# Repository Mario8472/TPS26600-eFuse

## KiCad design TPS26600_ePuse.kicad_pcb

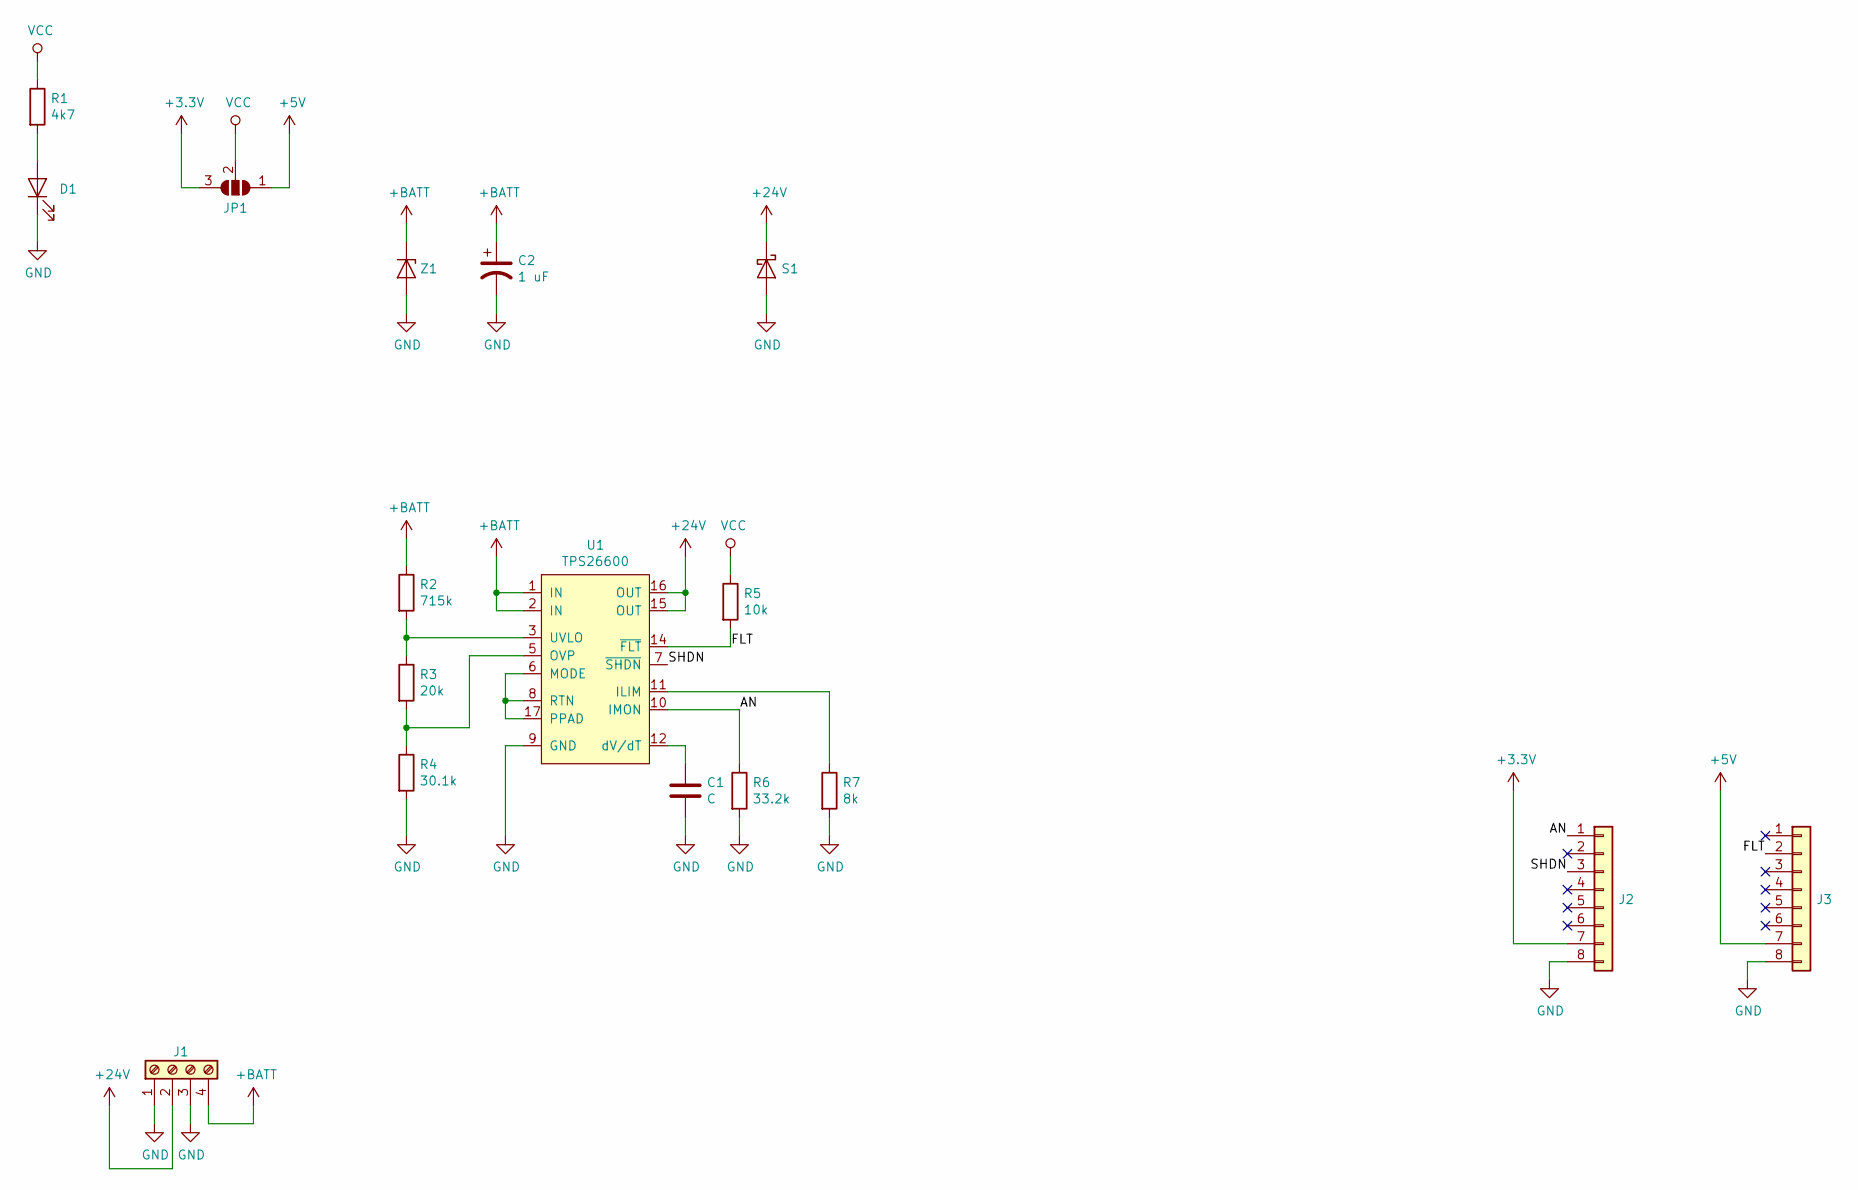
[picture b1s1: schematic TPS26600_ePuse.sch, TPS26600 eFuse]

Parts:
C1: C; C_0805_2012Metric
C2: 1 uF; C_1206_3216Metric
D1: LED; LED_0805_2012Metric
J1: Screw_Terminal_01x04; PCB_Screw_Terminal_5.08_4ways
J2, J3: Conn_01x08; PinHeader_1x08_P2.54mm_Vertical
JP1: SolderJumper_3_Open; Jumper_0805
R1: 4k7; R_0805_2012Metric
R2: 715k; R_0805_2012Metric
R3: 20k; R_0805_2012Metric
R4: 30.1k; R_0805_2012Metric
R5: 10k; R_0805_2012Metric
R6: 33.2k; R_0805_2012Metric
R7: 8k; R_0805_2012Metric
S1: D_Schottky; D_SMA
U1: TPS26600; HTSSOP-16-1EP_4.4x5mm_P0.65mm_EP3x3mm
Z1: D_Zener; D_SMA

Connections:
+3V3: J2.7, JP1.3 (B)
+5V: J3.7, JP1.1 (A)
+24V: J1.2, S1.1 (K), U1.15 (OUT), U1.16 (OUT)
+BATT: C2.1, J1.4, R2.1, U1.1 (IN), U1.2 (IN), Z1.1 (K)
/AN: J2.1, R6.1, U1.10 (IMON)
/FLT: J3.2, R5.2, U1.14 (~FLT)
/SHDN: J2.3, U1.7 (~SHDN)
GND: C1.2, C2.2, D1.1 (K), J1.1, J1.3, J2.8, J3.8, R4.2, R6.2, R7.2, S1.2 (A), U1.9 (GND), Z1.2 (A)
unnamed: C1.1, U1.12 (dV/dT)
unnamed: D1.2 (A), R1.2
unnamed: R2.2, R3.1, U1.3 (UVLO)
unnamed: R3.2, R4.1, U1.5 (OVP)
unnamed: R7.1, U1.11 (ILIM)
unnamed: U1.6 (MODE), U1.8 (RTN), U1.17 (PPAD)
VCC: JP1.2 (C), R1.1, R5.1

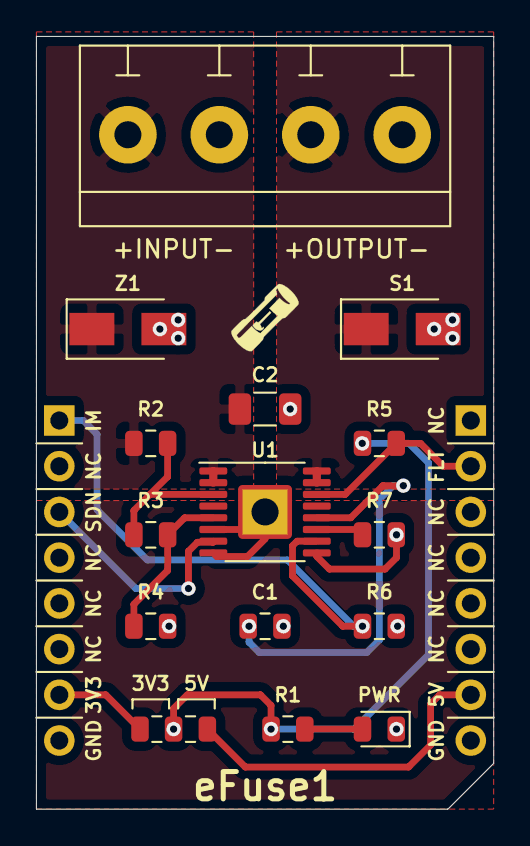
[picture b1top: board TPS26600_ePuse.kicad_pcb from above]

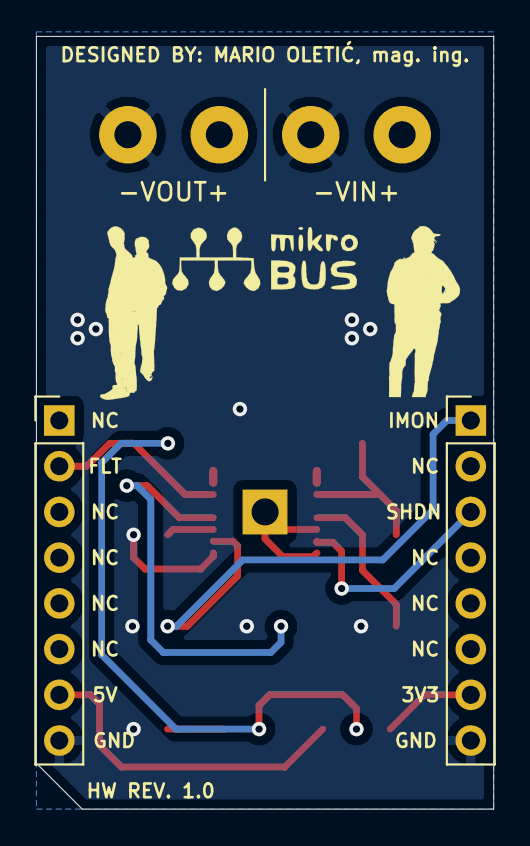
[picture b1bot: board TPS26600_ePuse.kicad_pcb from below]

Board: 2 copper layers, 25.4 x 42.9 mm, 17 parts (2 on the bottom side), 15 nets.
